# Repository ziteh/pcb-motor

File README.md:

# PCB Motor

AF-PMSM (axial flux permanent magnet synchronous machine) PCB stator, inspired by the [sabanekko3/pcb_stator_v2](https://github.com/sabanekko3/pcb_stator_v2) and [CarlBugeja/PCB-Motor-v4](https://github.com/CarlBugeja/PCB-Motor-v4).

## Note

### Slot/Pole Topology

In the design of a PMSM, selecting the slot/pole topology is the first step [5].

The Star of Slot (SOS) method is commonly used for this purpose.

- Pole: The number of permanent magnets.
- Slot: The number of coil slots.

The slot-to-pole relationship can be classified into:

- Integer-slot
- Fractional-slot

For a three-phase motor, the relationship can be analyzed as follows:

$$
Q=\frac{N_{s}}{3\cdot 2p}
$$

where:
- $Q$ is the slot per pole per phase.
- $N_s$ is the total number of slots.
- $p$ is the number of pole pairs.

### Winding

Based on [1], the winding layout can be categorized into the following types:
1. Concentric
2. Parallel
3. Radial [2]
4. Arc
5. Unequal width parallel

The design in [1] features a 144-slot , 16-pole configuration with 3 slots per pole per phase on a double-layer PCB. The PCB has a thickness of 1mm, an air gap of 1mm, and a copper thickness of 70μm.

According to the findings, radial and concentric windings exhibit the highest torque and induced phase voltage. However, among these, the concentric winding has the highest losses and THD (Total Harmonic Distortion). The radial winding has the lowest THD, making it suitable for high-precision applications. The parallel winding has the lowest resistance, whereas the unequal width parallel winding reduces phase resistance by 17% compared to the standard parallel winding while maintaining the same induced phase voltage and output torque.

The study in [3], based on the results of [1], selected the radial winding layout for PCB motor design. However, an axial unequal-width winding design was adopted. The primary advantage of using unequal width traces is that the larger copper cross-sectional area results in lower phase resistance compared to equal-width traces. Additionally, increasing the total copper area helps reduce thermal stress by providing lower thermal resistance.

The motor specifications are as follows:
- Pole count: 20
- PCB thickness: 2mm
- PCB layers: 6
- Copper thickness: 140μm
- Air gap: 1mm

### Rotor

For permanent magnet rotors, the Halbach array can be considered.

## Ref

1. [Comparison of PCB winding topologies for axial-flux permanent magnet synchronous machines](https://doi.org/10.1049/iet-epa.2020.0622)
2. [Comparative analysis of wave winding topologies and performance characteristics in ultra-thin printed circuit board axial-flux permanent magnet machine](https://doi.org/10.1049/iet-epa.2018.5417)
3. [Mechanical and Thermal Design of an Optimized PCB Motor for an Integrated Motor Drive System With GaNFETs](https://doi.org/10.1109/TEC.2022.3213896)
4. [Axial-flux permanent-magnet machine modeling, design, simulation and analysis](https://www.researchgate.net/publication/228847506_Axial-flux_permanent-magnet_machine_modeling_design_simulation_and_analysis)
5. [Analysis of slot-pole combination of fractional-slots PMSM for embedded applications](https://doi.org/10.1109/ACEMP.2011.6490669)
6. [Analytical Study and Comparison of Electromagnetic Characteristics of 8-Pole 9-Slot and 8-Pole 12-Slot Permanent Magnet Synchronous Machines Considering Rotor Eccentricity](https://doi.org/10.3390/electronics10162036)
7. [Design and Testing of PMSM for Aerospace EMA Applications](http://dx.doi.org/10.1109/IECON.2018.8591318)
8. [プリント基板コイル（PCBステータ）を使ってモーターを作る会　その１ - さばと根っこな製作記](https://sabanekko2.hatenablog.com/entry/2023/03/06/130205)

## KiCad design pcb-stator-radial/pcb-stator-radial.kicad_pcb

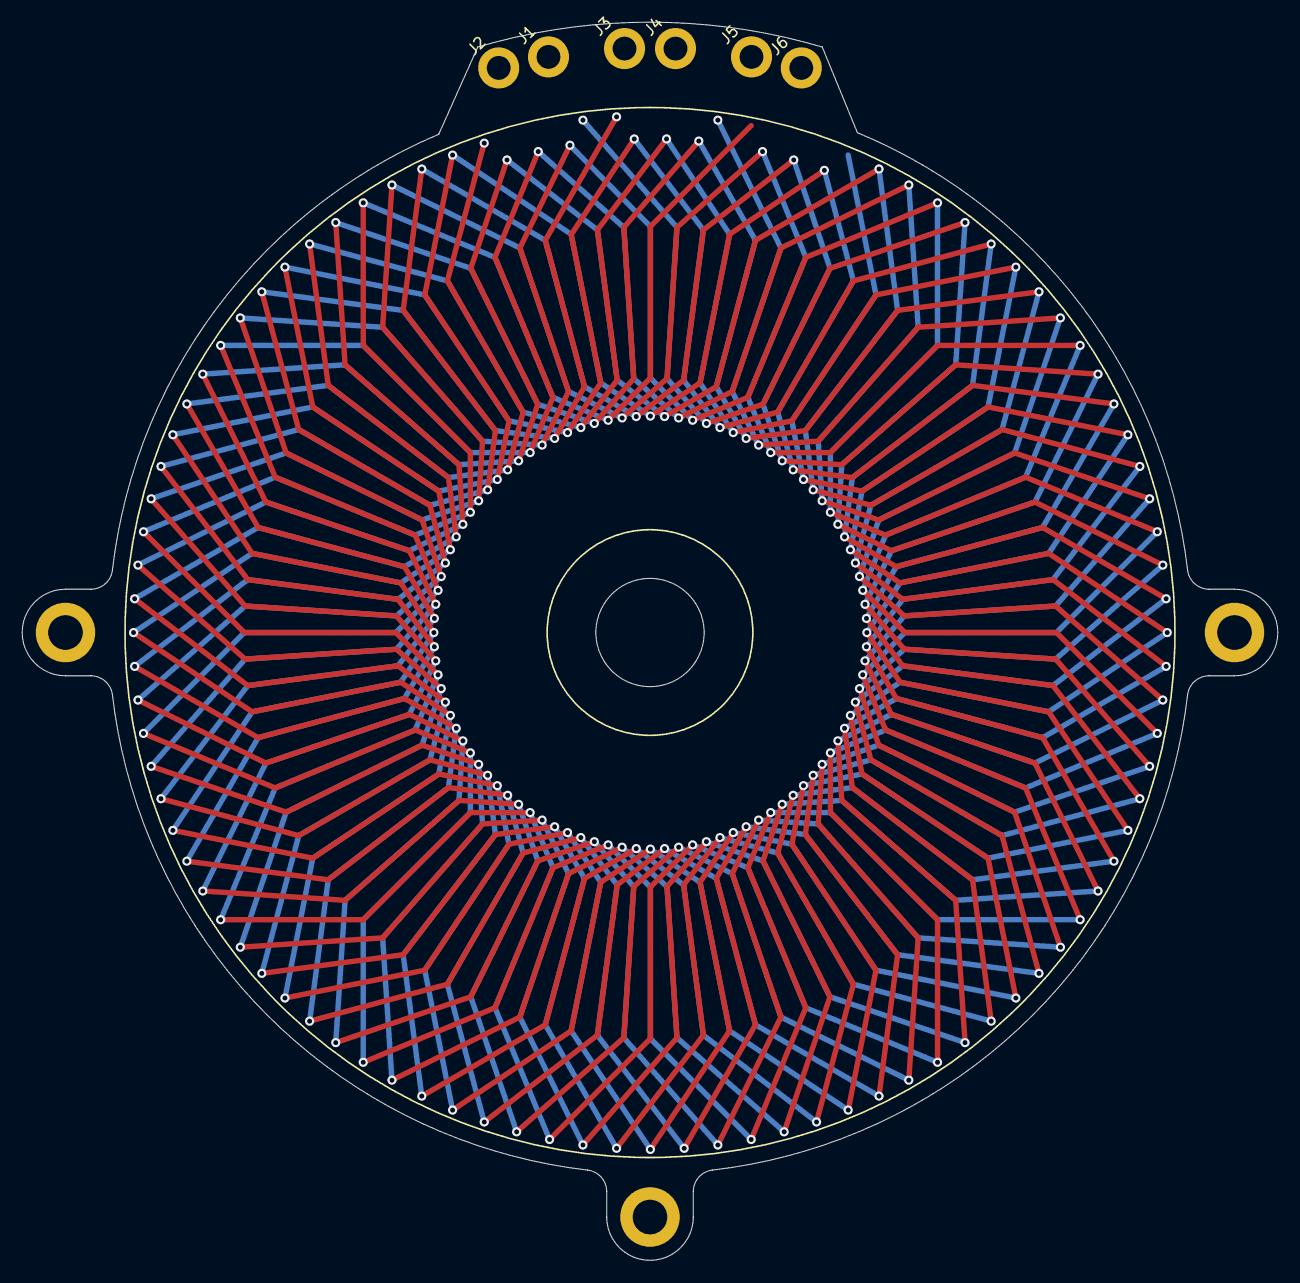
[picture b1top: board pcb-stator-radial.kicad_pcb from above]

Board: 2 copper layers, 116.0 x 114.4 mm, 9 parts (0 on the bottom side), 3 nets.

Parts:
H2, H3, H7: MountingHole_Pad; MountingHole_3.2mm_M3_ISO14580_Pad
J1: A+; MountingHole_2.2mm_M2_ISO14580_Pad
J2: A-; MountingHole_2.2mm_M2_ISO14580_Pad
J3: B+; MountingHole_2.2mm_M2_ISO14580_Pad
J4: B-; MountingHole_2.2mm_M2_ISO14580_Pad
J5: C+; MountingHole_2.2mm_M2_ISO14580_Pad
J6: C-; MountingHole_2.2mm_M2_ISO14580_Pad

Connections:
/A_Phase: J1.1, J2.1
/B_Phase: J3.1, J4.1
/C_Phase: J5.1, J6.1

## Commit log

2023-09-12 Init commit
2023-09-12 Create LICENSE
2023-09-12 Move KiCad files into folder
2023-11-04 Routed (96 slot, 16 pole)
2025-02-16 add note
2025-04-17 chore: add `.gitattributes`
